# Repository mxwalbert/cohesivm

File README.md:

# COHESIVM: Combinatorial h+/e- Sample Investigation using Voltaic Measurements

## Introduction

The COHESIVM Python package provides a generalized framework for conducting combinatorial voltaic measurements in
scientific research and development. The modular architecture enables researchers to adapt it to diverse experimental 
setups by extending its components to support custom configurations. These components are cohesively put together in an
[``Experiment``](https://cohesivm.readthedocs.io/en/latest/reference/experiment.html#cohesivm.experiment.Experiment) class which runs compatibility checks, manages data storage, and 
executes the measurements.

### Key Features:

- **Modular Design:** COHESIVM adopts a module-oriented approach where components such as measurement devices
  ([``Device``](https://cohesivm.readthedocs.io/en/latest/reference/devices.html#cohesivm.devices.Device)), contacting interfaces ([``Interface``](https://cohesivm.readthedocs.io/en/latest/reference/interfaces.html#cohesivm.interfaces.Interface)), and measurement
  routines ([``Measurement``](https://cohesivm.readthedocs.io/en/latest/reference/measurements.html#cohesivm.measurements.Measurement)) are abstracted into interchangeable units. This modular
  architecture enhances flexibility in experimental setups and makes it easy to add new component implementations.
  The tutorials in the [documentation](https://cohesivm.readthedocs.io/en/latest/) provide an extensive description of implementing custom components.
- **Combinatorial Flexibility:** By abstracting the class for the contacting interface, COHESIVM enables diverse
  configurations for sample investigation. The [MA8X8 measurement array](https://github.com/mxwalbert/cohesivm/tree/main/hardware/ma8x8), as implemented in the current core 
  version, is only one example for an electrode contact array. Researchers can add custom implementations of the 
  [``Interface``](https://cohesivm.readthedocs.io/en/latest/reference/interfaces.html#cohesivm.interfaces.Interface) class to support other configurations or, for example, robotic contacting 
  systems.
- **Data Handling:** Collected data is stored in a structured [HDF5](https://www.hdfgroup.org/solutions/hdf5/) database
  format using the [``Database``](https://cohesivm.readthedocs.io/en/latest/reference/database.html#cohesivm.database.Database) class, ensuring efficient data management and accessibility.
  [``Metadata``](https://cohesivm.readthedocs.io/en/latest/reference/database.html#cohesivm.database.Metadata) is collected based on the [DCMI standard](http://purl.org/dc/terms/) which is
  extended by COHESIVM-specific metadata terms.
- **Analysis and GUIs:** Alongside the measurement routines, analysis functions and plots can be implemented, extending
  the [``Analysis``](https://cohesivm.readthedocs.io/en/latest/reference/analysis.html#cohesivm.analysis.Analysis) base class. Together with the graphical user interface (also available for
  conducting experiments and reviewing the database contents), initial screening of the data is facilitated.
 
## Table of Contents
- [Getting Started](#getting-started)
- [Graphical User Interfaces](#graphical-user-interfaces)
- [Examples](#examples)
- [Package Reference](#package-reference)
- [License](#license)
- [Contributing](#contributing)
- [Citation](#citation)
- [Contact](#contact)

## Getting Started

### Dependencies

The current core version of COHESIVM is tested for Python 3.9–3.12 and requires the following dependencies:

- h5py (~=3.8)
- numpy (~=1.21)
- matplotlib (~=3.7)
- tqdm (~=4.65)

Apart from the core package, [extras](https://packaging.python.org/en/latest/tutorials/installing-packages/#installing-extras) 
exist for modules with additional dependencies (check the [``pyproject.toml``](https://github.com/mxwalbert/cohesivm/blob/main/pyproject.toml) for a complete listing):

| Extra   | Module                    | Dependency       |
|---------|---------------------------|------------------|
| gui     | cohesivm.gui              | bqplot~=0.12     |
| ma8x8   | cohesivm.interfaces.ma8x8 | pyserial~=3.5    |
| ossila  | cohesivm.devices.ossila   | xtralien~=2.10   |
| agilent | cohesivm.devices.agilent  | pyvisa~=1.13     |
| full    | –                         | *all from above* |

### Installation

#### Using pip
To install the core COHESIVM package from the Python Package Index (PyPI), simply run:

```console
pip install cohesivm
```

This command will download and install the latest stable version of COHESIVM and its core dependencies.

> [!IMPORTANT]
> 
> If you want to use the GUIs inside your [Jupyter](https://jupyter.org/) environment, make sure to specify the 
> ``gui`` extra:
> 
> ```console
> pip install cohesivm[gui]
> ```

#### Cloning from GitHub
If you want to install the development version of the package from the GitHub repository, follow these steps:
1. **Clone** the repository to your local machine:
    ```console
    git clone https://github.com/mxwalbert/cohesivm.git
    ```
2. **Navigate** into the cloned directory:
    ```console
    cd cohesivm
    ```
3. **Install** the package and its dependencies:
    ```console
    pip install .[dev]
    ```

### Configuration

A ``config.ini`` file should be placed in the root of your project to configure the hardware ports/addresses of the
contact interfaces and measurement devices. Some DCMI metadata terms also need to be defined there. COHESIVM implements
a config parser which allows to access these values, e.g.:

```pycon
>>> import cohesivm
>>> cohesivm.config.get_option('DCMI', 'creator')
Dow, John
```

#### Template

[A preconfigured file](https://github.com/mxwalbert/cohesivm/blob/main/config.ini) with the currently implemented 
interfaces and devices can be copied from the repository, or you can create your own from this template:

```ini
# This file is used to configure the project as well as the devices and interfaces (e.g., COM ports, addresses, ...).

# METADATA ------------------------------------------------------------------------------------------------------------

[DCMI]
# The following options correspond to the terms defined by the Dublin Core Metadata Initiative.
# See https://purl.org/dc/terms/ for detailed descriptions.
publisher = "Your Company Ltd."
creator = "Dow, John"
rights = <https://link.to/licence>
subject = "modular design"; "combinatorial flexibility"; "data handling"; "analysis and gui"

# ---------------------------------------------------------------------------------------------------------------------

# INTERFACES ----------------------------------------------------------------------------------------------------------

[NAME_OF_USB_INTERFACE]
com_port = 42

# ---------------------------------------------------------------------------------------------------------------------

# DEVICES -------------------------------------------------------------------------------------------------------------

[NAME_OF_NETWORK_DEVICE]
address = localhost
port = 8888
timeout = 0.1

# ---------------------------------------------------------------------------------------------------------------------
```

The names of the sections (e.g., ``NAME_OF_USB_INTERFACE``) must be unique but can be chosen freely since they are 
referenced manually. The options (e.g., ``com_port``), on the other hand, should follow the signature of the class 
constructor to use them efficiently. For example, an [``Interface``](https://cohesivm.readthedocs.io/en/latest/reference/interfaces.html#cohesivm.interfaces.Interface) implementation 
``DemoInterface`` which requires the ``com_port`` parameter could be initialized using the configuration template 
from above:

```python
interface = DemoInterface(**config.get_section('NAME_OF_USB_INTERFACE'))
```

#### Example

In a common scenario, you probably want to configure multiple devices to use them at once. Let's consider the case 
where you need two [``OssilaX200``](https://cohesivm.readthedocs.io/en/latest/reference/devices.html#cohesivm.devices.ossila.OssilaX200) devices which are both connected via USB. Then, in the 
``DEVICES`` part of the configuration, you would define two distinctive sections and set the required ``address`` 
option:

```ini
# DEVICES -------------------------------------------------------------------------------------------------------------

[OssilaX200_1]
address = COM4

[OssilaX200_2]
address = COM5

# ---------------------------------------------------------------------------------------------------------------------
```

To initialize the devices, you could do something similar to the [Basic Usage](#basic-usage) 
example:

```python
from cohesivm import config
from cohesivm.devices.ossila import OssilaX200
smu1 = OssilaX200.VoltageSMUChannel()
device1 = OssilaX200.OssilaX200(channels=[smu1], **config.get_section('OssilaX200_1'))
smu2 = OssilaX200.VoltageSMUChannel()
device2 = OssilaX200.OssilaX200(channels=[smu2], **config.get_section('OssilaX200_2'))
```

### Basic Usage

> [!IMPORTANT]
> If you only installed the core package, the following example will raise import errors from missing dependencies. 
> To use the [``Agilent4156C``](https://cohesivm.readthedocs.io/en/latest/reference/devices.html#cohesivm.devices.agilent.Agilent4156C), [``MA8X8``](https://cohesivm.readthedocs.io/en/latest/reference/interfaces.html#cohesivm.interfaces.ma8x8.MA8X8), and 
> [``OssilaX200``](https://cohesivm.readthedocs.io/en/latest/reference/devices.html#cohesivm.devices.ossila.OssilaX200) classes, you need to install the ``agilent``, ``ma8x8``, and ``ossila`` 
> extras, respectively. To add all dependencies at once, install the ``full`` extra with this command:
> ```console
> pip install cohesivm[full]
> ```

With working implementations of the main components ([``Device``](https://cohesivm.readthedocs.io/en/latest/reference/devices.html#cohesivm.devices.Device),
[``Interface``](https://cohesivm.readthedocs.io/en/latest/reference/interfaces.html#cohesivm.interfaces.Interface), [``Measurement``](https://cohesivm.readthedocs.io/en/latest/reference/measurements.html#cohesivm.measurements.Measurement)), setting up and running an
experiment only takes a few lines of code:

```python
from cohesivm import config
from cohesivm.database import Database, Dimensions
from cohesivm.experiment import Experiment
from cohesivm.progressbar import ProgressBar
from cohesivm.devices.agilent import Agilent4156C
from cohesivm.interfaces import MA8X8
from cohesivm.measurements.iv import CurrentVoltageCharacteristic

# Create a new or load an existing database
db = Database('Test.h5')

# Configure the components
smu = Agilent4156C.SweepVoltageSMUChannel()
device = Agilent4156C.Agilent4156C(channels=[smu], **config.get_section('Agilent4156C'))
interface = MA8X8(com_port=config.get_option('MA8X8', 'com_port'), pixel_dimensions=Dimensions.Circle(radius=0.425))
measurement = CurrentVoltageCharacteristic(start_voltage=-2.0, end_voltage=2.0, voltage_step=0.01, illuminated=True)

# Combine the components in an experiment
experiment = Experiment(
    database=db,
    device=device,
    interface=interface,
    measurement=measurement,
    sample_id='test_sample_42',
    selected_contacts=None
)

# Optionally set up a progressbar
pbar = ProgressBar(experiment)

# Run the experiment
with pbar.show():
    experiment.quickstart()
```

If you want to change the measurement device to a different one, you only need to adjust the lines for the
[``Channel``](https://cohesivm.readthedocs.io/en/latest/reference/channels.html#cohesivm.channels.Channel) and the [``Device``](https://cohesivm.readthedocs.io/en/latest/reference/devices.html#cohesivm.devices.Device) accordingly:

```python
from cohesivm.devices.ossila import OssilaX200
smu = OssilaX200.VoltageSMUChannel()
device = OssilaX200.OssilaX200(channels=[smu], **config.get_section('OssilaX200'))
```

## Graphical User Interfaces

If you work with [Jupyter](https://jupyter.org/), you may use the Graphical User Interfaces (GUIs) which are implemented
in the form of [Jupyter Widgets](https://ipywidgets.readthedocs.io/en/stable/).

Currently, three GUIs are available:

### Experiment GUI

On the left panel "Control", you see the current [``ExperimentState``](https://cohesivm.readthedocs.io/en/latest/reference/experiment.html#cohesivm.experiment.ExperimentState), followed by a 
representation of the [``Interface``](https://cohesivm.readthedocs.io/en/latest/reference/interfaces.html#cohesivm.interfaces.Interface) and the control buttons at the bottom. The circles are 
annotated with the [``contact_ids``](https://cohesivm.readthedocs.io/en/latest/reference/interfaces.html#cohesivm.interfaces.Interface.contact_ids) and the colors correspond to their current state. 
On the right panel "Plot", the currently running [``Measurement``](https://cohesivm.readthedocs.io/en/latest/reference/measurements.html#cohesivm.measurements.Measurement) is displayed. The plot is 
automatically updated as soon as new measurement data arrives in the 
[``data_stream``](https://cohesivm.readthedocs.io/en/latest/reference/experiment.html#cohesivm.experiment.Experiment.data_stream) of the [``Experiment``](https://cohesivm.readthedocs.io/en/latest/reference/experiment.html#cohesivm.experiment.Experiment) object.

### Database GUI

This GUI enables to display and filter the measurement data which is stored in an HDF5 file. At the top, you select to
display the data grouped in terms of the [``Measurement``](https://cohesivm.readthedocs.io/en/latest/reference/measurements.html#cohesivm.measurements.Measurement) or by the
[``sample_name``](https://cohesivm.readthedocs.io/en/latest/reference/experiment.html#cohesivm.experiment.Experiment.sample_name) of the [``Experiment``](https://cohesivm.readthedocs.io/en/latest/reference/experiment.html#cohesivm.experiment.Experiment) object. If you
choose the former one, you may additionally filter the data by means of measurement parameters. The button to the very
right of each data row enables you to copy the dataset path, to access it in the [``Database``](https://cohesivm.readthedocs.io/en/latest/reference/database.html#cohesivm.database.Database).

### Analysis GUI

Similar to the Experiment GUI, the "Interface" panel represents the contacts with their respective IDs. They can be
clicked to display the measured data in the "Plot" panel to the right. There, the arrows can be used to switch between
[``functions``](https://cohesivm.readthedocs.io/en/latest/reference/analysis.html#cohesivm.analysis.Analysis.functions) that are defined in the [``Analysis``](https://cohesivm.readthedocs.io/en/latest/reference/analysis.html#cohesivm.analysis.Analysis) class. The
results of the [``functions``](https://cohesivm.readthedocs.io/en/latest/reference/analysis.html#cohesivm.analysis.Analysis.functions), which are also implemented there, are shown in the table
below.

Detailed guides to work with the GUIs can be found in the [documentation](https://cohesivm.readthedocs.io/en/latest/).

## Examples

> [!NOTE]
> For a practical example, read the [Real-World Example](https://cohesivm.readthedocs.io/en/latest/tutorials/real-world_example.html).

### Run an Experiment

Follow the [Basic Usage](#basic-usage) example to set up and run an 
[``Experiment``](https://cohesivm.readthedocs.io/en/latest/reference/experiment.html#cohesivm.experiment.Experiment). If you do not have all components ready yet, follow these tutorials:

- [Implement a Device](https://cohesivm.readthedocs.io/en/latest/tutorials/device.html)
- [Implement an Interface](https://cohesivm.readthedocs.io/en/latest/tutorials/interface.html)
- [Implement a Measurement](https://cohesivm.readthedocs.io/en/latest/tutorials/measurement.html)

To follow the other examples, you may just run the code from the [Basic Usage](#basic-usage) 
example even if you do not have access to the hardware. This will fail but create an HDF5 file and store an empty 
dataset entry.

### Manage the Data

#### List Datasets

After you collected some data and stored it in an HDF5 file, you can use the [``Database``](https://cohesivm.readthedocs.io/en/latest/reference/database.html#cohesivm.database.Database) class
to work with it. First, initialise the [``Database``](https://cohesivm.readthedocs.io/en/latest/reference/database.html#cohesivm.database.Database) object and list the samples which are stored
there:

```pycon
>>> from cohesivm.database import Database
>>> db = Database('Test.h5')
>>> db.get_sample_ids()
['test_sample_42']
```

This is exactly the [``sample_id``](https://cohesivm.readthedocs.io/en/latest/reference/experiment.html#cohesivm.experiment.Experiment.sample_id) which was specified when the
[``Experiment``](https://cohesivm.readthedocs.io/en/latest/reference/experiment.html#cohesivm.experiment.Experiment) was configured, and it can be used to retrieve the actual
``dataset`` path in the [``Database``](https://cohesivm.readthedocs.io/en/latest/reference/database.html#cohesivm.database.Database) object:

```pycon
>>> db.filter_by_sample_id('test_sample_42')
['/CurrentVoltageCharacteristic/55d96687ee75aa11:26464063430fe52f:a69a946e7a02e547:c8965a35118ce6fc:67a8bfb44702cfc7:8131a44cea4d4bb8/2024-07-01T10:44:59.033161-test_sample_42']
```

The resulting list contains the path strings for all [``Dataset``](https://cohesivm.readthedocs.io/en/latest/reference/database.html#cohesivm.database.Dataset)s with the specified
[``sample_id``](https://cohesivm.readthedocs.io/en/latest/reference/experiment.html#cohesivm.experiment.Experiment.sample_id) (currently only one entry). These strings get quite long because they
contain the [``name``](https://cohesivm.readthedocs.io/en/latest/reference/measurements.html#cohesivm.measurements.Measurement.name) of the [``Measurement``](https://cohesivm.readthedocs.io/en/latest/reference/measurements.html#cohesivm.measurements.Measurement)
procedure, followed by a hashed representation of the [``settings``](https://cohesivm.readthedocs.io/en/latest/reference/measurements.html#cohesivm.measurements.Measurement.settings) dictionary,
and finally the datetime combined with the [``sample_id``](https://cohesivm.readthedocs.io/en/latest/reference/experiment.html#cohesivm.experiment.Experiment.sample_id). 

#### Access Metadata

With a ``dataset`` path, you can retrieve information from the [``Metadata``](https://cohesivm.readthedocs.io/en/latest/reference/database.html#cohesivm.database.Metadata) object which was 
created by the [``Experiment``](https://cohesivm.readthedocs.io/en/latest/reference/experiment.html#cohesivm.experiment.Experiment):

```pycon
>>> dataset = db.filter_by_sample_id('test_sample_42')[0]
>>> metadata = db.load_metadata(dataset)
>>> metadata.sample_id, metadata.device, metadata.interface, metadata.measurement
('test_sample_42', 'Agilent4156C', 'MA8X8', 'CurrentVoltageCharacteristic')
```

Creating a new [``Dataset``](https://cohesivm.readthedocs.io/en/latest/reference/database.html#cohesivm.database.Dataset) is less trivial because you need a fully qualified 
[``Metadata``](https://cohesivm.readthedocs.io/en/latest/reference/database.html#cohesivm.database.Metadata) object, which asks for a large number of arguments. Anyway, this is usually 
handled by the [``Experiment``](https://cohesivm.readthedocs.io/en/latest/reference/experiment.html#cohesivm.experiment.Experiment) class which also guarantees that the specified components 
are compatible.

As a test, you can use the [``Metadata``](https://cohesivm.readthedocs.io/en/latest/reference/database.html#cohesivm.database.Metadata) object from above to initialize a new 
[``Dataset``](https://cohesivm.readthedocs.io/en/latest/reference/database.html#cohesivm.database.Dataset) in the database:

```pycon
>>> db.initialize_dataset(metadata)
'/CurrentVoltageCharacteristic/55d96687ee75aa11:26464063430fe52f:a69a946e7a02e547:c8965a35118ce6fc:67a8bfb44702cfc7:8131a44cea4d4bb8/2024-07-01T10:46:05.910371-test_sample_42'
```

This yields practically the same ``dataset`` path as before, only the datetime is different.

#### Work with Data Entries

Adding data entries to a [``Dataset``](https://cohesivm.readthedocs.io/en/latest/reference/database.html#cohesivm.database.Dataset) is fairly simple since you only need to specify the 
``dataset`` path and the ``contact_id`` (alongside the ``data`` of course):

```pycon
>>> db.save_data(np.array([1], dtype=[('Quantity (Unit)', int)]), dataset)
>>> db.save_data(np.array([42], dtype=[('Quantity (Unit)', int)]), dataset, '1')
```

You should use a [structured array](https://numpy.org/doc/stable/user/basics.rec.html) by providing a dtype with named
fields because it facilitates to store the quantity and the unit alongside the data.

Finally, you can load a data entry by specifying the ``contact_id``, several entries by using a list of IDs, or load an 
entire [``Dataset``](https://cohesivm.readthedocs.io/en/latest/reference/database.html#cohesivm.database.Dataset), including the [``Metadata``](https://cohesivm.readthedocs.io/en/latest/reference/database.html#cohesivm.database.Metadata):

```pycon
>>> db.load_data(dataset, '0')
array([(1,)], dtype=[('Quantity (Unit)', '<i4')])
>>> db.load_data(dataset, ['0', '1'])
[array([(1,)], dtype=[('Quantity (Unit)', '<i4')]),
 array([(42,)], dtype=[('Quantity (Unit)', '<i4')])]
>>> db.load_dataset(dataset)
({'0': array([(1,)], dtype=[('Quantity (Unit)', '<i4')]),
  '1': array([(42,)], dtype=[('Quantity (Unit)', '<i4')])},
 'Metadata(CurrentVoltageCharacteristic, Agilent4156C, MA8X8)')
```

To work with a [structured array](https://numpy.org/doc/stable/user/basics.rec.html), you need to know the names of the 
fields which are stored in the ``dtype`` property. With this name, you can access the data of an individual field:

```pycon
>>> a = np.array([(1, 42)], dtype=[('Quantity1 (Unit1)', int), ('Quantity2 (Unit2)', int)])
>>> a.dtype
dtype([('Quantity1 (Unit1)', '<i4'), ('Quantity2 (Unit2)', '<i4')])
>>> a['Quantity1 (Unit1)']
array([1])
```

The [``Database``](https://cohesivm.readthedocs.io/en/latest/reference/database.html#cohesivm.database.Database) class also implements methods for filtering datasets based on the
[``settings``](https://cohesivm.readthedocs.io/en/latest/reference/measurements.html#cohesivm.measurements.Measurement.settings) of the [``Measurement``](https://cohesivm.readthedocs.io/en/latest/reference/measurements.html#cohesivm.measurements.Measurement). Check out the 
documentation of the [``filter_by_settings``](https://cohesivm.readthedocs.io/en/latest/reference/database.html#cohesivm.database.Database.filter_by_settings) and 
[``filter_by_settings_batch``](https://cohesivm.readthedocs.io/en/latest/reference/database.html#cohesivm.database.Database.filter_by_settings_batch) to learn more.

### Analyse the Results

The [``Analysis``](https://cohesivm.readthedocs.io/en/latest/reference/analysis.html#cohesivm.analysis.Analysis) is tightly bound with the [``Measurement``](https://cohesivm.readthedocs.io/en/latest/reference/measurements.html#cohesivm.measurements.Measurement) because
this will determine how the data is shaped and which features you want to extract from it. Therefore, the base class
should be extended as explained in this tutorial:

- [Implement an Analysis](https://cohesivm.readthedocs.io/en/latest/tutorials/analysis.html)

However, in the following example, the base class will be used to show the basic functionality.

#### Generate Data

Since the [``MA8X8``](https://cohesivm.readthedocs.io/en/latest/reference/interfaces.html#cohesivm.interfaces.MA8X8) interface was used in the previous examples, the initialized
[``Dataset``](https://cohesivm.readthedocs.io/en/latest/reference/database.html#cohesivm.database.Dataset) should be filled with data accordingly. With the HDF5 file from 
the [Basic Usage](#basic-usage) example, this script should do the job:

```python
import numpy as np
from cohesivm.database import Database

# load existing data and corresponding metadata
db = Database('Test.h5')
dataset = db.filter_by_sample_id('test_sample_42')[0]
metadata = db.load_metadata(dataset)

# create a new dataset to not interfere with previous examples
dataset = db.initialize_dataset(metadata)

# iterate over contact_ids and save data arrays
for contact_id in metadata.contact_ids:
    db.save_data(np.array(range(10), dtype=[('Voltage (V)', float)]), dataset, contact_id)

# load the data
data, metadata = db.load_dataset(dataset)
```

#### Define Functions

Next, [``functions``](https://cohesivm.readthedocs.io/en/latest/reference/analysis.html#cohesivm.analysis.Analysis.functions) and [``plots``](https://cohesivm.readthedocs.io/en/latest/reference/analysis.html#cohesivm.analysis.Analysis.plots) must be defined:

```pycon
>>> def maximum(contact_id: str) -> float:
...     return max(data[contact_id]['Voltage (V)'])
>>> functions = {'Maximum': maximum}
>>> plots = {}  # will be spared for simplicity (refer to the tutorial instead)
```

This approach seems too complex for what the function does, but it makes sense if you consider that this should be
implemented in a separate [``Analysis``](https://cohesivm.readthedocs.io/en/latest/reference/analysis.html#cohesivm.analysis.Analysis) class. There, the data is stored as a property and the
[``functions``](https://cohesivm.readthedocs.io/en/latest/reference/analysis.html#cohesivm.analysis.Analysis.functions) (i.e., methods) have direct access to it. Due to the use of 
[structured arrays](https://numpy.org/doc/stable/user/basics.rec.html), the label also needs to be stated explicitly. But, again, this will normally be available as 
a property of the class.

#### With vs. without Metadata

In the following, the class is initialized with and without using the [``Metadata``](https://cohesivm.readthedocs.io/en/latest/reference/database.html#cohesivm.database.Metadata) from the
dataset. The former approach has the advantage that all available fields could be accessed by the
[``functions``](https://cohesivm.readthedocs.io/en/latest/reference/analysis.html#cohesivm.analysis.Analysis.functions), e.g., values that are stored in the
[``measurement_settings``](https://cohesivm.readthedocs.io/en/latest/reference/database.html#cohesivm.database.Metadata.measurement_settings).

```pycon
>>> from cohesivm.analysis import Analysis
# without metadata, the contact_position_dict must be provided
>>> analysis = Analysis(functions, plots, data, metadata.contact_position_dict)
# with metadata, additional metadata fields can be used in the analysis
>>> analysis = Analysis(functions, plots, (data, metadata))
>>> analysis.metadata.measurement_settings['illuminated']
True
```

#### Use the Class

The main purposes of the [``Analysis``](https://cohesivm.readthedocs.io/en/latest/reference/analysis.html#cohesivm.analysis.Analysis) are bundling functions for quick data analysis 
and providing the framework for the [Analysis GUI](https://cohesivm.readthedocs.io/en/latest/guis/analysis.html). But it is also useful to generate maps 
of analysis results:

```pycon
>>> analysis.generate_result_maps('Maximum')[0]
array([[9., 9., 9., 9., 9., 9., 9., 9.],
       [9., 9., 9., 9., 9., 9., 9., 9.],
       [9., 9., 9., 9., 9., 9., 9., 9.],
       [9., 9., 9., 9., 9., 9., 9., 9.],
       [9., 9., 9., 9., 9., 9., 9., 9.],
       [9., 9., 9., 9., 9., 9., 9., 9.],
       [9., 9., 9., 9., 9., 9., 9., 9.],
       [9., 9., 9., 9., 9., 9., 9., 9.]])
```

As expected, the maximum value of the generated data is placed in a 2D numpy array on locations corresponding to
the [``contact_positions``](https://cohesivm.readthedocs.io/en/latest/reference/Interface.html#interfaces.Interface.contact_positions).

## Package Reference

The package reference can be found in the [documentation](https://cohesivm.readthedocs.io/en/latest/).

## License
The source code of this project is licensed under the [MIT license](LICENSE), and the hardware design and schematics 
are licensed under the [CERN OHL v2 Permissive license](hardware/LICENSE).

## Contributing

The contributing guidelines can be found [here](CONTRIBUTING.md).

## Citation

If you use this package for your research, please cite:

> Wolf et al., (2025). _COHESIVM: Combinatorial h+/e- Sample Investigation using Voltaic Measurements._ 
> Journal of Open Source Software, 10(106), 7291, 
> [https://doi.org/10.21105/joss.07291](https://doi.org/10.21105/joss.07291)

**BibTeX**

```
@article{
    Wolf2025, 
    doi = {10.21105/joss.07291}, 
    url = {https://doi.org/10.21105/joss.07291}, 
    year = {2025}, 
    publisher = {The Open Journal}, 
    volume = {10}, 
    number = {106}, 
    pages = {7291}, 
    author = {Maximilian Wolf and Selina Götz and Georg K.h. Madsen and Theodoros Dimopoulos}, 
    title = {COHESIVM: Combinatorial h+/e- Sample Investigation using Voltaic Measurements}, 
    journal = {Journal of Open Source Software} 
}
```

## Contact

This project is developed by AIT Austrian Institute of Technology and TU Wien.

For questions, feedback, or support regarding COHESIVM, feel free to [open an issue](https://github.com/mxwalbert/cohesivm/issues) 
or reach out via email at [maximilian.wolf@ait.ac.at](mailto:maximilian.wolf@ait.ac.at?subject=COHESIVM).

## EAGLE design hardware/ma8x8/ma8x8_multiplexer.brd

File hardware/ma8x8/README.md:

# MA8X8: Measurement Array 8x8 interface

This interface consist of 64 front contacts and a single back contact on an area of 25&nbsp;mm x 25&nbsp;mm. It is 
controlled by an Arduino Nano Every board which is connected through a serial COM port. The implementation of this 
interface is documented here: [``cohesivm.interfaces.MA8X8``](https://cohesivm.readthedocs.io/en/latest/reference/interfaces.html#cohesivm.interfaces.MA8X8).

## Contact Mask

As depicted on the image to the left, the contact mask can be used to manufacture masks for sputtering or evaporation 
of contacts onto 25&nbsp;mm x 25&nbsp;mm substrates. The pads on the corners and edges are used for the single back 
contact, while the circular pads will be switched through by the multiplexer.

## Interface

The contact interface, as depicted on the image to the middle, is made up of 64 + 8 pogo pins which are soldered to a 
custom-made PCB. On the bottom of the board are the pin headers for the connection to the multiplexer.

## Multiplexer

The actual switching between the contacts is carried out by the multiplexer board (on the image to the right). This PCB 
is powered by an Arduino Nano, houses 64 relays and 4 I/O extender.

## Files

- [ma8x8_contact_mask.brd](./ma8x8_contact_mask.brd)
- [ma8x8_interface.brd](./ma8x8_interface.brd)
- [ma8x8_interface.sch](./ma8x8_interface.sch)
- [ma8x8_multiplexer.brd](./ma8x8_multiplexer.brd)
- [ma8x8_multiplexer.sch](./ma8x8_multiplexer.sch)
- [ma8x8_multiplexer.ino](./ma8x8_multiplexer.ino)

The *.brd and *.sch files are the board and schematics CAD files, respectively. To render the boards in 3D there exist 
a couple of free online services, e.g., [here](https://www.application-art.de/) and [here](https://www.altium.com/viewer).
The *.ino file is the firmware for the Arduino Nano which works with the implemented MA8X8 interface.

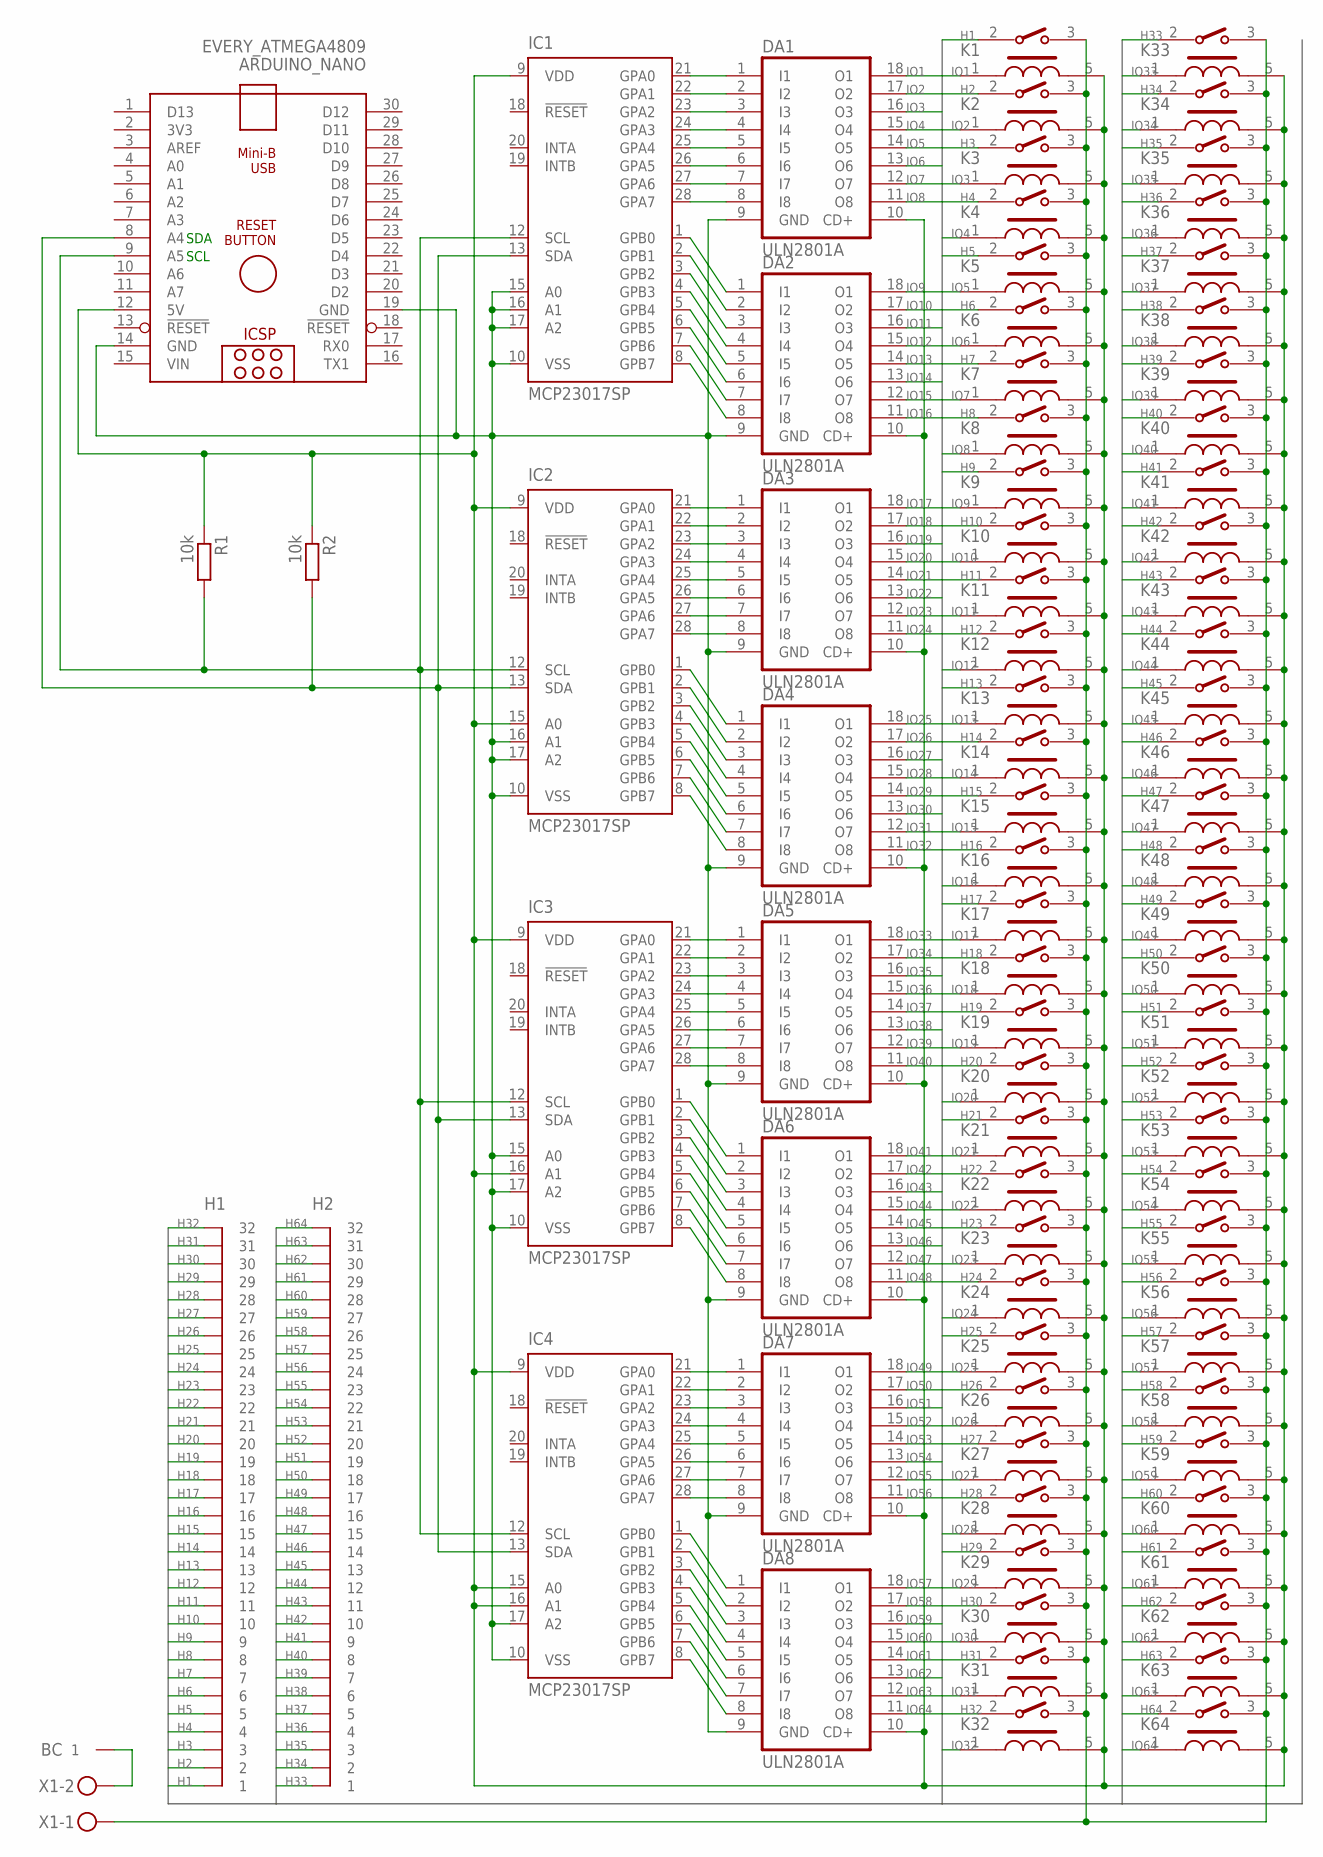
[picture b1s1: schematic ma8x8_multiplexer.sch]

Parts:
ARDUINO_NANO: EVERY_ATMEGA4809; ARDUINO_NANO
BC: 310-47-101-41-001000
DA1, DA2, DA3, DA4, DA5, DA6, DA7, DA8: ULN2801A; DIL18
H1, H2: 310-47-132-41-001000
IC1, IC2, IC3, IC4: MCP23017SP; DIL28-3
K1, K2, K3, K4, K5, K6, K7, K8, K9, K10, K11, K12, K13, K14, K15, K16, K17, K18, K19, K20, K21, K22, K23, K24, K25, K26, K27, K28, K29, K30, K31, K32, K33, K34, K35, K36, K37, K38, K39, K40, K41, K42, K43, K44, K45, K46, K47, K48, K49, K50, K51, K52, K53, K54, K55, K56, K57, K58, K59, K60, K61, K62, K63, K64: OMRON_G5Q-1A4-EU_DC5; OMRON_G5Q-1A4-EU_DC5_0
R1, R2: 10k; R1206
X1: MKDSN1,5/2-5,08

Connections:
5V: ARDUINO_NANO.12 (5V), DA1.10 (CD+), DA2.10 (CD+), DA3.10 (CD+), DA4.10 (CD+), DA5.10 (CD+), DA6.10 (CD+), DA7.10 (CD+), DA8.10 (CD+), IC1.9 (VDD), IC2.9 (VDD), IC2.15 (A0), IC3.9 (VDD), IC3.16 (A1), IC4.9 (VDD), IC4.15 (A0), IC4.16 (A1), K1.5, K2.5, K3.5, K4.5, K5.5, K6.5, K7.5, K8.5, K9.5, K10.5, K11.5, K12.5, K13.5, K14.5, K15.5, K16.5, K17.5, K18.5, K19.5, K20.5, K21.5, K22.5, K23.5, K24.5, K25.5, K26.5, K27.5, K28.5, K29.5, K30.5, K31.5, K32.5, K33.5, K34.5, K35.5, K36.5, K37.5, K38.5, K39.5, K40.5, K41.5, K42.5, K43.5, K44.5, K45.5, K46.5, K47.5, K48.5, K49.5, K50.5, K51.5, K52.5, K53.5, K54.5, K55.5, K56.5, K57.5, K58.5, K59.5, K60.5, K61.5, K62.5, K63.5, K64.5, R1.1, R2.1
BC: BC.1, X1.2
FC: K1.3, K2.3, K3.3, K4.3, K5.3, K6.3, K7.3, K8.3, K9.3, K10.3, K11.3, K12.3, K13.3, K14.3, K15.3, K16.3, K17.3, K18.3, K19.3, K20.3, K21.3, K22.3, K23.3, K24.3, K25.3, K26.3, K27.3, K28.3, K29.3, K30.3, K31.3, K32.3, K33.3, K34.3, K35.3, K36.3, K37.3, K38.3, K39.3, K40.3, K41.3, K42.3, K43.3, K44.3, K45.3, K46.3, K47.3, K48.3, K49.3, K50.3, K51.3, K52.3, K53.3, K54.3, K55.3, K56.3, K57.3, K58.3, K59.3, K60.3, K61.3, K62.3, K63.3, K64.3, X1.1
GND: ARDUINO_NANO.14 (GND), ARDUINO_NANO.19 (GND), DA1.9 (GND), DA2.9 (GND), DA3.9 (GND), DA4.9 (GND), DA5.9 (GND), DA6.9 (GND), DA7.9 (GND), DA8.9 (GND), IC1.10 (VSS), IC1.15 (A0), IC1.16 (A1), IC1.17 (A2), IC2.10 (VSS), IC2.16 (A1), IC2.17 (A2), IC3.10 (VSS), IC3.15 (A0), IC3.17 (A2), IC4.10 (VSS), IC4.17 (A2)
H1: H1.1, K1.2
H2: H1.2, K2.2
H3: H1.3, K3.2
H4: H1.4, K4.2
H5: H1.5, K5.2
H6: H1.6, K6.2
H7: H1.7, K7.2
H8: H1.8, K8.2
H9: H1.9, K9.2
H10: H1.10, K10.2
H11: H1.11, K11.2
H12: H1.12, K12.2
H13: H1.13, K13.2
H14: H1.14, K14.2
H15: H1.15, K15.2
H16: H1.16, K16.2
H17: H1.17, K17.2
H18: H1.18, K18.2
H19: H1.19, K19.2
H20: H1.20, K20.2
H21: H1.21, K21.2
H22: H1.22, K22.2
H23: H1.23, K23.2
H24: H1.24, K24.2
H25: H1.25, K25.2
H26: H1.26, K26.2
H27: H1.27, K27.2
H28: H1.28, K28.2
H29: H1.29, K29.2
H30: H1.30, K30.2
H31: H1.31, K31.2
H32: H1.32, K32.2
H33: H2.1, K33.2
H34: H2.2, K34.2
H35: H2.3, K35.2
H36: H2.4, K36.2
H37: H2.5, K37.2
H38: H2.6, K38.2
H39: H2.7, K39.2
H40: H2.8, K40.2
H41: H2.9, K41.2
H42: H2.10, K42.2
H43: H2.11, K43.2
H44: H2.12, K44.2
H45: H2.13, K45.2
H46: H2.14, K46.2
H47: H2.15, K47.2
H48: H2.16, K48.2
H49: H2.17, K49.2
H50: H2.18, K50.2
H51: H2.19, K51.2
H52: H2.20, K52.2
H53: H2.21, K53.2
H54: H2.22, K54.2
H55: H2.23, K55.2
H56: H2.24, K56.2
H57: H2.25, K57.2
H58: H2.26, K58.2
H59: H2.27, K59.2
H60: H2.28, K60.2
H61: H2.29, K61.2
H62: H2.30, K62.2
H63: H2.31, K63.2
H64: H2.32, K64.2
IO1: DA1.18 (O1), K1.1
IO2: DA1.17 (O2), K2.1
IO3: DA1.16 (O3), K3.1
IO4: DA1.15 (O4), K4.1
IO5: DA1.14 (O5), K5.1
IO6: DA1.13 (O6), K6.1
IO7: DA1.12 (O7), K7.1
IO8: DA1.11 (O8), K8.1
IO9: DA2.18 (O1), K9.1
IO10: DA2.17 (O2), K10.1
IO11: DA2.16 (O3), K11.1
IO12: DA2.15 (O4), K12.1
IO13: DA2.14 (O5), K13.1
IO14: DA2.13 (O6), K14.1
IO15: DA2.12 (O7), K15.1
IO16: DA2.11 (O8), K16.1
IO17: DA3.18 (O1), K17.1
IO18: DA3.17 (O2), K18.1
IO19: DA3.16 (O3), K19.1
IO20: DA3.15 (O4), K20.1
IO21: DA3.14 (O5), K21.1
IO22: DA3.13 (O6), K22.1
IO23: DA3.12 (O7), K23.1
IO24: DA3.11 (O8), K24.1
IO25: DA4.18 (O1), K25.1
IO26: DA4.17 (O2), K26.1
IO27: DA4.16 (O3), K27.1
IO28: DA4.15 (O4), K28.1
IO29: DA4.14 (O5), K29.1
IO30: DA4.13 (O6), K30.1
IO31: DA4.12 (O7), K31.1
IO32: DA4.11 (O8), K32.1
IO33: DA5.18 (O1), K33.1
IO34: DA5.17 (O2), K34.1
IO35: DA5.16 (O3), K35.1
IO36: DA5.15 (O4), K36.1
IO37: DA5.14 (O5), K37.1
IO38: DA5.13 (O6), K38.1
IO39: DA5.12 (O7), K39.1
IO40: DA5.11 (O8), K40.1
IO41: DA6.18 (O1), K41.1
IO42: DA6.17 (O2), K42.1
IO43: DA6.16 (O3), K43.1
IO44: DA6.15 (O4), K44.1
IO45: DA6.14 (O5), K45.1
IO46: DA6.13 (O6), K46.1
IO47: DA6.12 (O7), K47.1
IO48: DA6.11 (O8), K48.1
IO49: DA7.18 (O1), K49.1
IO50: DA7.17 (O2), K50.1
IO51: DA7.16 (O3), K51.1
IO52: DA7.15 (O4), K52.1
IO53: DA7.14 (O5), K53.1
IO54: DA7.13 (O6), K54.1
IO55: DA7.12 (O7), K55.1
IO56: DA7.11 (O8), K56.1
IO57: DA8.18 (O1), K57.1
IO58: DA8.17 (O2), K58.1
IO59: DA8.16 (O3), K59.1
IO60: DA8.15 (O4), K60.1
IO61: DA8.14 (O5), K61.1
IO62: DA8.13 (O6), K62.1
IO63: DA8.12 (O7), K63.1
IO64: DA8.11 (O8), K64.1
unnamed: DA1.1 (I1), IC1.21 (GPA0)
unnamed: DA1.2 (I2), IC1.22 (GPA1)
unnamed: DA1.3 (I3), IC1.23 (GPA2)
unnamed: DA1.4 (I4), IC1.24 (GPA3)
unnamed: DA1.5 (I5), IC1.25 (GPA4)
unnamed: DA1.6 (I6), IC1.26 (GPA5)
unnamed: DA1.7 (I7), IC1.27 (GPA6)
unnamed: DA1.8 (I8), IC1.28 (GPA7)
unnamed: DA2.1 (I1), IC1.1 (GPB0)
unnamed: DA2.2 (I2), IC1.2 (GPB1)
unnamed: DA2.3 (I3), IC1.3 (GPB2)
unnamed: DA2.4 (I4), IC1.4 (GPB3)
unnamed: DA2.5 (I5), IC1.5 (GPB4)
unnamed: DA2.6 (I6), IC1.6 (GPB5)
unnamed: DA2.7 (I7), IC1.7 (GPB6)
unnamed: DA2.8 (I8), IC1.8 (GPB7)
unnamed: DA3.1 (I1), IC2.21 (GPA0)
unnamed: DA3.2 (I2), IC2.22 (GPA1)
unnamed: DA3.3 (I3), IC2.23 (GPA2)
unnamed: DA3.4 (I4), IC2.24 (GPA3)
unnamed: DA3.5 (I5), IC2.25 (GPA4)
unnamed: DA3.6 (I6), IC2.26 (GPA5)
unnamed: DA3.7 (I7), IC2.27 (GPA6)
unnamed: DA3.8 (I8), IC2.28 (GPA7)
unnamed: DA4.8 (I8), IC2.8 (GPB7)
unnamed: DA4.7 (I7), IC2.7 (GPB6)
unnamed: DA4.6 (I6), IC2.6 (GPB5)
unnamed: DA4.5 (I5), IC2.5 (GPB4)
unnamed: DA4.4 (I4), IC2.4 (GPB3)
unnamed: DA4.3 (I3), IC2.3 (GPB2)
unnamed: DA4.2 (I2), IC2.2 (GPB1)
unnamed: DA4.1 (I1), IC2.1 (GPB0)
unnamed: DA5.1 (I1), IC3.21 (GPA0)
unnamed: DA5.2 (I2), IC3.22 (GPA1)
unnamed: DA5.3 (I3), IC3.23 (GPA2)
unnamed: DA5.4 (I4), IC3.24 (GPA3)
unnamed: DA5.5 (I5), IC3.25 (GPA4)
unnamed: DA5.6 (I6), IC3.26 (GPA5)
unnamed: DA5.7 (I7), IC3.27 (GPA6)
unnamed: DA5.8 (I8), IC3.28 (GPA7)
unnamed: DA6.1 (I1), IC3.1 (GPB0)
unnamed: DA6.2 (I2), IC3.2 (GPB1)
unnamed: DA6.3 (I3), IC3.3 (GPB2)
unnamed: DA6.4 (I4), IC3.4 (GPB3)
unnamed: DA6.5 (I5), IC3.5 (GPB4)
unnamed: DA6.6 (I6), IC3.6 (GPB5)
unnamed: DA6.7 (I7), IC3.7 (GPB6)
unnamed: DA6.8 (I8), IC3.8 (GPB7)
unnamed: DA7.1 (I1), IC4.21 (GPA0)
unnamed: DA7.2 (I2), IC4.22 (GPA1)
unnamed: DA7.3 (I3), IC4.23 (GPA2)
unnamed: DA7.4 (I4), IC4.24 (GPA3)
unnamed: DA7.5 (I5), IC4.25 (GPA4)
unnamed: DA7.6 (I6), IC4.26 (GPA5)
unnamed: DA7.7 (I7), IC4.27 (GPA6)
unnamed: DA7.8 (I8), IC4.28 (GPA7)
unnamed: DA8.1 (I1), IC4.1 (GPB0)
unnamed: DA8.2 (I2), IC4.2 (GPB1)
unnamed: DA8.3 (I3), IC4.3 (GPB2)
unnamed: DA8.4 (I4), IC4.4 (GPB3)
unnamed: DA8.5 (I5), IC4.5 (GPB4)
unnamed: DA8.6 (I6), IC4.6 (GPB5)
unnamed: DA8.7 (I7), IC4.7 (GPB6)
unnamed: DA8.8 (I8), IC4.8 (GPB7)
SCL: ARDUINO_NANO.9 (A5), IC1.12 (SCL), IC2.12 (SCL), IC3.12 (SCL), IC4.12 (SCL), R1.2
SDA: ARDUINO_NANO.8 (A4), IC1.13 (SDA), IC2.13 (SDA), IC3.13 (SDA), IC4.13 (SDA), R2.2
VIN: ARDUINO_NANO.15 (VIN)

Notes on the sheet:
SDA
SCL

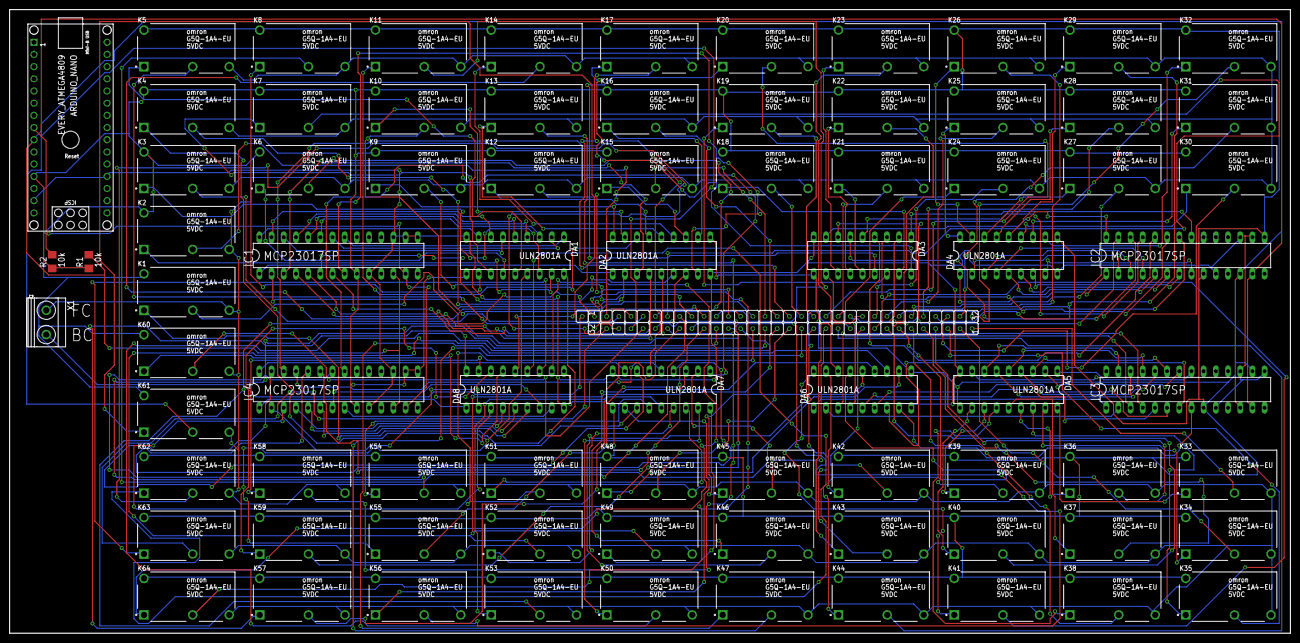
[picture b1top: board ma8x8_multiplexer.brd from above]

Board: 2 copper layers, 267.0 x 130.0 mm, 83 parts (0 on the bottom side), 198 nets.

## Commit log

2023-06-01 Implementation of principal API components
2023-06-02 Changes type of pixel to str
2023-06-05 Refactored protected/private property names. Updated documentation.
2023-06-06 Refactored parent class initialization.
2023-06-07 Refactored _check_compatibility method.
2023-06-07 test iv and test experiment (compatibility error)
2023-06-13 Implemented tests for Ossila device. Refactored tests.
2023-06-13 Refactored experiment test.
2023-06-19 test experiment completed, corresponding changes in experiment.py and database.py
2023-06-20 Implemented gui and test_gui. Refactored tests.
2023-07-20 Implemented Agilent 4284A device and CV measurement. Refactored Ossila X200 device. Refactored tests and project structure. Added progressbar to data stream module. Added metadata to database record 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
2023-07-21 implemented iv analysis
2024-05-26 Implemented Agilent 4284A device and CV measurement. Refactored Ossila X200 device. Refactored tests and project structure. Added progressbar to data stream module. Added metadata to database record 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
2024-08-12 Initial release, heavily refactored, added documentation
2024-08-12 Resolve incorrect link parsing.
2024-08-12 Minor documentation changes.
2024-08-12 Added requirements.txt for readthedocs.io
2024-08-12 Corrected requirements.txt for readthedocs.io
2024-08-12 Corrected readthedocs link.
2024-08-13 Added MA8X8 hardware files and docu.
2024-08-13 Automated composing README.md.
2024-08-13 Corrected workflows.
2024-08-13 Scrap automated README.md for now.
2024-08-13 Added README.md
2024-08-19 Added JOSS paper
2024-08-20 Paper corrections
2024-08-20 Removed SweepMe from references
2024-08-20 Moved contributing guidelines to a separate file. Updated DOIs in paper.bib.
2024-11-17 docs: fix incorrect dev instructions in README (#1)
2024-11-17 docs: added a "getting involved" (contact & contributing) section. added an admonition in tutorials to promote contributions. (#2)
2024-11-17 docs: added an example in the README's configuration section (#3)
2024-11-17 docs: added a real-world example in the tutorials to give a high-level description of using COHESIVM. (#4)
2024-11-17 docs: added a dependencies section. added admonitions in the basic usage example and the GUI description. (#5)
2024-11-18 docs/paper: linked the tutorials for component implementation and MA8X8 interface description in the README introduction. made the key features and advantages in the JOSS paper more explicit. referen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
2024-11-23 removed unused test file (#7)
2024-11-23 removed future reference in JOSS paper (#6)
2025-01-03 re-phrasing usage description in paper.md
2025-01-27 implemented joss review
2025-02-16 added JOSS citation, structured examples documentation
2025-06-17 implemented CV analysis; fixed CV measurement and Agilent4284A device
2025-06-17 fixed datetime in database/GUI; added delete_sample database and prepared operation in GUI; fixed progressbar and added test; bugfixes.
2025-06-17 removed paper workflow; fixed robust_datetime_id_split method;

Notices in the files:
README.md:
License:
The source code of this project is licensed under the [MIT license](LICENSE), and the hardware design and schematics
are licensed under the [CERN OHL v2 Permissive license](hardware/LICENSE).
If you use this package for your research, please cite:
> Wolf et al., (2025). _COHESIVM: Combinatorial h+/e- Sample Investigation using Voltaic Measurements._
> Journal of Open Source Software, 10(106), 7291,
> [https://doi.org/10.21105/joss.07291](https://doi.org/10.21105/joss.07291)
BibTeX
@article{
Wolf2025,
doi = {10.21105/joss.07291},
url = {https://doi.org/10.21105/joss.07291},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
